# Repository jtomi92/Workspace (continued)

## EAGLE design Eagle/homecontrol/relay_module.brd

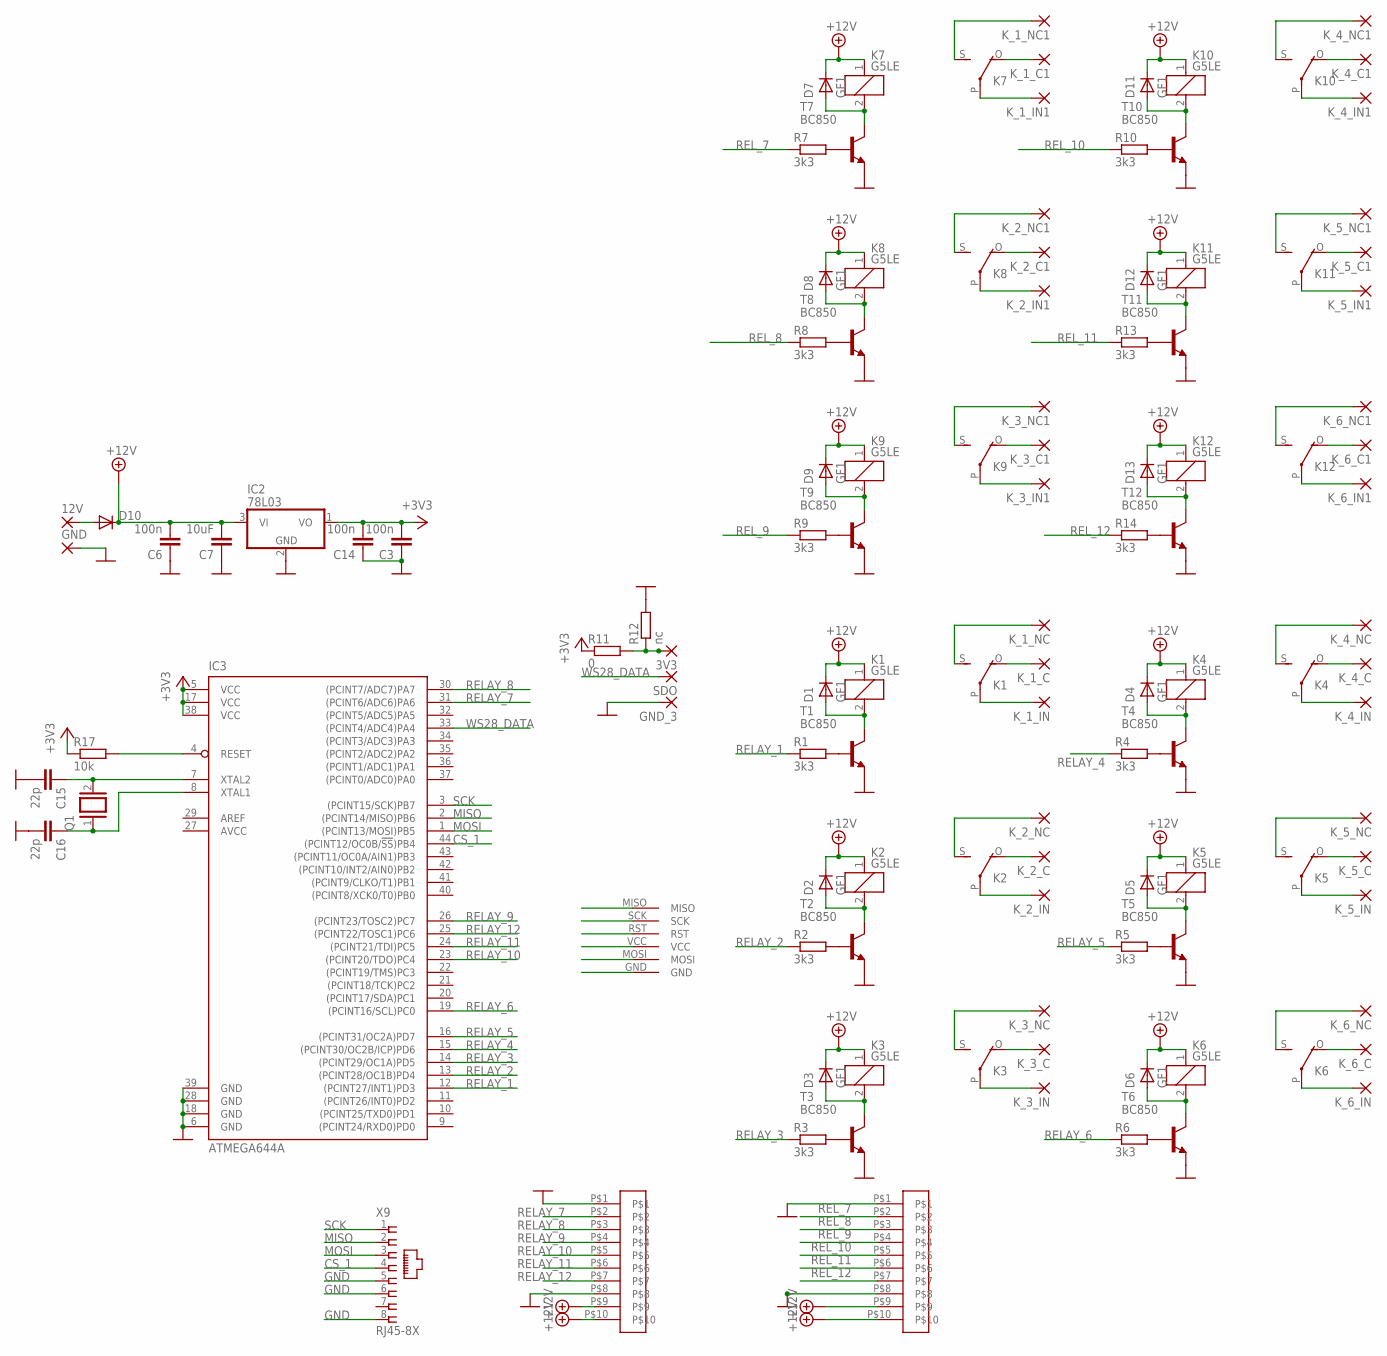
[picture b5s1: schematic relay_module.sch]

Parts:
3V3: 2,15/1,0
12V: 2,54/0,8
C3, C6, C14: 100n; C1206
C7: 10uF; C1206
C15, C16: 22p; C1206
D1, D2, D3, D4, D5, D6, D7, D8, D9, D11, D12, D13: GF1; SMA-DO214AC
D10: 1N4148DO35-10; DO35-10
GND: 2,54/0,8
GND_3: 2,15/1,0
IC2: 78L03; TO92
IC3: ATMEGA644A; TQFP44
K1, K2, K3, K4, K5, K6, K7, K8, K9, K10, K11, K12: G5LE
K_1_C, K_1_C1, K_1_IN, K_1_IN1, K_1_NC, K_1_NC1, K_2_C, K_2_C1, K_2_IN, K_2_IN1, K_2_NC, K_2_NC1, K_3_C, K_3_C1, K_3_IN, K_3_IN1, K_3_NC, K_3_NC1, K_4_C, K_4_C1, K_4_IN, K_4_IN1, K_4_NC, K_4_NC1, K_5_C, K_5_C1, K_5_IN, K_5_IN1, K_5_NC, K_5_NC1, K_6_C, K_6_C1, K_6_IN, K_6_IN1, K_6_NC, K_6_NC1: 2,54/0,8
Q1: XTAL/S; QS
R1, R2, R3, R4, R5, R6, R7, R8, R9, R10, R13, R14: 3k3; M3216
R11: 0; M3216
R12: nc; M3216
R17: 10k; M3216
SDO: 2,15/1,0
T1, T2, T3, T4, T5, T6, T7, T8, T9, T10, T11, T12: BC850; SOT23
U$1, U$3: 10P
U$2: AVR_ISP
X9: RJ45-8X; RJ45-NO-SHIELD

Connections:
+3V3: C3.2, C14.2, IC2.1 (VO), IC3.5 (VCC), IC3.17 (VCC), IC3.38 (VCC), R11.1, R17.1, U$2.VCC
+12V: C6.2, C7.2, D1.K (C), D2.K (C), D3.K (C), D4.K (C), D5.K (C), D6.K (C), D7.K (C), D8.K (C), D9.K (C), D10.C, D11.K (C), D12.K (C), D13.K (C), IC2.3 (VI), K1.1, K2.1, K3.1, K4.1, K5.1, K6.1, K7.1, K8.1, K9.1, K10.1, K11.1, K12.1, U$1.P$9, U$1.P$10, U$3.P$9, U$3.P$10
AVCC: IC3.27 (AVCC)
CS_1: IC3.44 ((PCINT12/OC0B/!SS!)PB4), X9.4
GND: C3.1, C6.1, C7.1, C14.1, C15.2, C16.2, GND.1, GND_3.1, IC2.2 (GND), IC3.6 (GND), IC3.18 (GND), IC3.28 (GND), IC3.39 (GND), R12.2, T1.2 (E), T2.2 (E), T3.2 (E), T4.2 (E), T5.2 (E), T6.2 (E), T7.2 (E), T8.2 (E), T9.2 (E), T10.2 (E), T11.2 (E), T12.2 (E), U$1.P$1, U$1.P$8, U$2.GND, U$3.P$1, U$3.P$8, X9.5, X9.6, X9.8
MISO: IC3.2 ((PCINT14/MISO)PB6), U$2.MISO, X9.2
MOSI: IC3.1 ((PCINT13/MOSI)PB5), U$2.MOSI, X9.3
unnamed: R1.2, T1.1 (B)
unnamed: D1.A, K1.2, T1.3 (C)
unnamed: K1.S, K_1_NC.1
unnamed: K1.P, K_1_IN.1
unnamed: K1.O, K_1_C.1
unnamed: R2.2, T2.1 (B)
unnamed: D2.A, K2.2, T2.3 (C)
unnamed: K2.P, K_2_IN.1
unnamed: K2.O, K_2_C.1
unnamed: K2.S, K_2_NC.1
unnamed: R3.2, T3.1 (B)
unnamed: D3.A, K3.2, T3.3 (C)
unnamed: K3.P, K_3_IN.1
unnamed: K3.O, K_3_C.1
unnamed: K3.S, K_3_NC.1
unnamed: R4.2, T4.1 (B)
unnamed: D4.A, K4.2, T4.3 (C)
unnamed: K4.P, K_4_IN.1
unnamed: K4.O, K_4_C.1
unnamed: K4.S, K_4_NC.1
unnamed: R5.2, T5.1 (B)
unnamed: D5.A, K5.2, T5.3 (C)
unnamed: K5.P, K_5_IN.1
unnamed: K5.O, K_5_C.1
unnamed: K5.S, K_5_NC.1
unnamed: R6.2, T6.1 (B)
unnamed: D6.A, K6.2, T6.3 (C)
unnamed: K6.P, K_6_IN.1
unnamed: K6.O, K_6_C.1
unnamed: K6.S, K_6_NC.1
unnamed: R7.2, T7.1 (B)
unnamed: D7.A, K7.2, T7.3 (C)
unnamed: K7.P, K_1_IN1.1
unnamed: K7.O, K_1_C1.1
unnamed: K7.S, K_1_NC1.1
unnamed: R8.2, T8.1 (B)
unnamed: D8.A, K8.2, T8.3 (C)
unnamed: K8.P, K_2_IN1.1
unnamed: K8.O, K_2_C1.1
unnamed: K8.S, K_2_NC1.1
unnamed: R9.2, T9.1 (B)
unnamed: D9.A, K9.2, T9.3 (C)
unnamed: K9.P, K_3_IN1.1
unnamed: K9.O, K_3_C1.1
unnamed: K9.S, K_3_NC1.1
unnamed: 3V3.1, R11.2, R12.1
unnamed: R10.2, T10.1 (B)
unnamed: D11.A, K10.2, T10.3 (C)
unnamed: K10.P, K_4_IN1.1
unnamed: 12V.1, D10.A
unnamed: K10.O, K_4_C1.1
unnamed: K10.S, K_4_NC1.1
unnamed: R13.2, T11.1 (B)
unnamed: D12.A, K11.2, T11.3 (C)
unnamed: K11.P, K_5_IN1.1
unnamed: K11.O, K_5_C1.1
unnamed: C15.1, IC3.7 (XTAL2), Q1.2
unnamed: K11.S, K_5_NC1.1
unnamed: R14.2, T12.1 (B)
unnamed: D13.A, K12.2, T12.3 (C)
unnamed: K12.P, K_6_IN1.1
unnamed: K12.O, K_6_C1.1
unnamed: K12.S, K_6_NC1.1
unnamed: C16.1, IC3.8 (XTAL1), Q1.1
RELAY_1: IC3.12 ((PCINT27/INT1)PD3), R1.1
RELAY_2: IC3.13 ((PCINT28/OC1B)PD4), R2.1
RELAY_3: IC3.14 ((PCINT29/OC1A)PD5), R3.1
RELAY_4: IC3.15 ((PCINT30/OC2B/ICP)PD6), R4.1
RELAY_5: IC3.16 ((PCINT31/OC2A)PD7), R5.1
RELAY_6: IC3.19 ((PCINT16/SCL)PC0), R6.1
RELAY_7: IC3.31 ((PCINT6/ADC6)PA6), U$1.P$2
RELAY_8: IC3.30 ((PCINT7/ADC7)PA7), U$1.P$3
RELAY_9: IC3.26 ((PCINT23/TOSC2)PC7), U$1.P$4
RELAY_10: IC3.23 ((PCINT20/TDO)PC4), U$1.P$5
RELAY_11: IC3.24 ((PCINT21/TDI)PC5), U$1.P$6
RELAY_12: IC3.25 ((PCINT22/TOSC1)PC6), U$1.P$7
REL_7: R7.1, U$3.P$2
REL_8: R8.1, U$3.P$3
REL_9: R9.1, U$3.P$4
REL_10: R10.1, U$3.P$5
REL_11: R13.1, U$3.P$6
REL_12: R14.1, U$3.P$7
RESET: IC3.4 (RESET), R17.2, U$2.RST
SCK: IC3.3 ((PCINT15/SCK)PB7), U$2.SCK, X9.1
WS28_DATA: IC3.33 ((PCINT4/ADC4)PA4), SDO.1

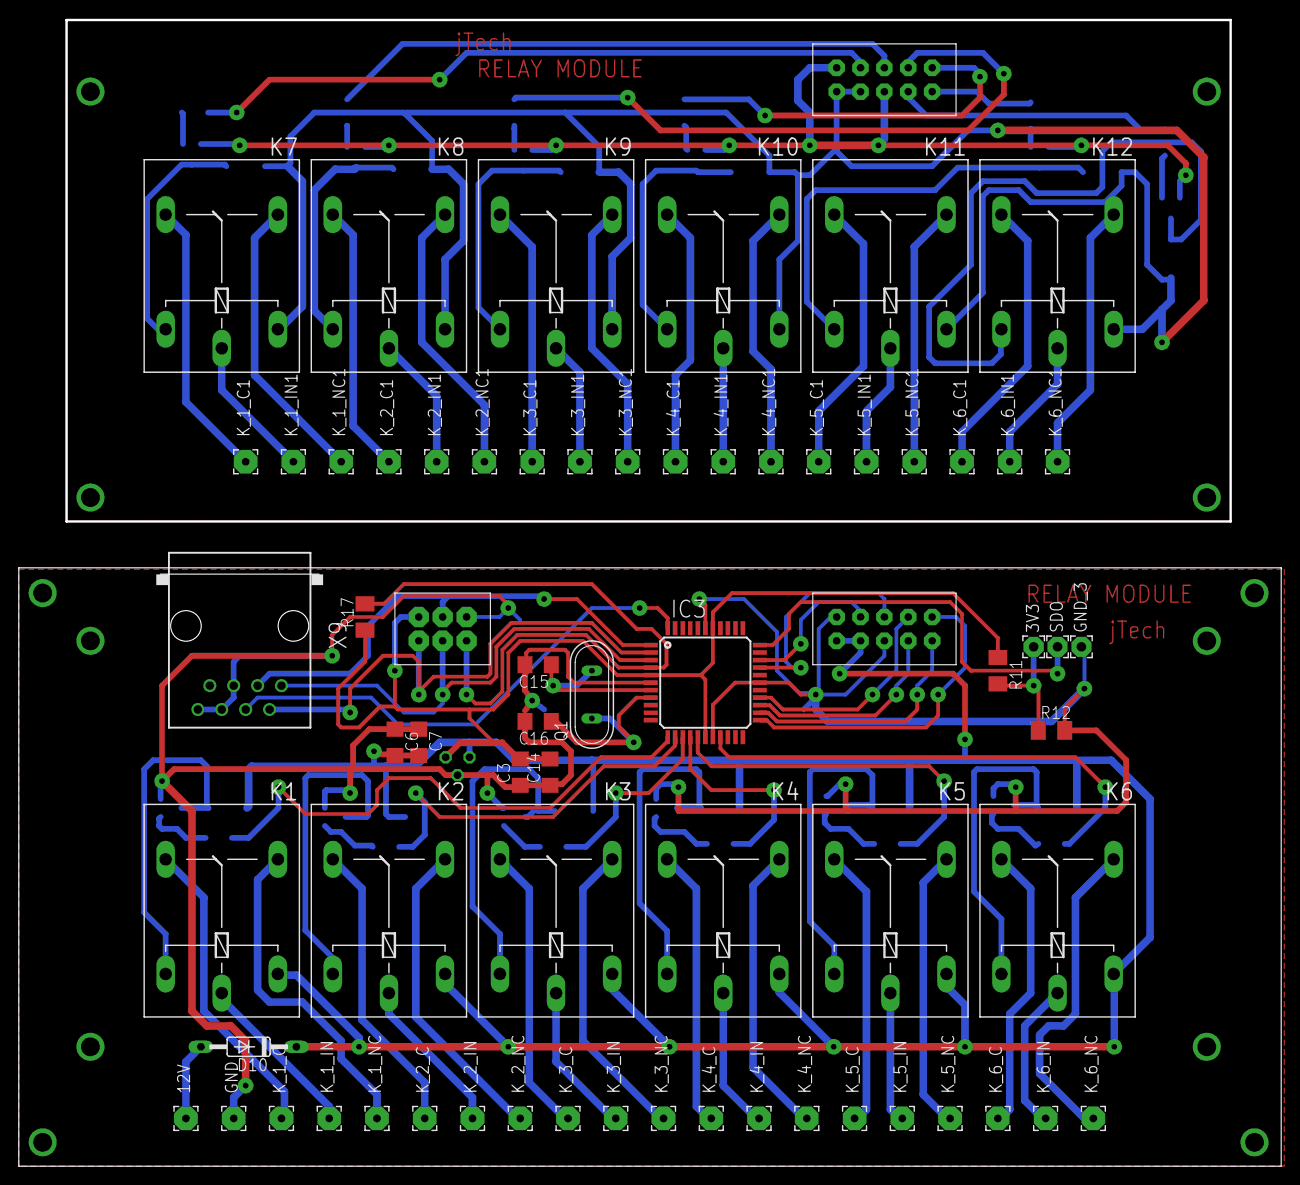
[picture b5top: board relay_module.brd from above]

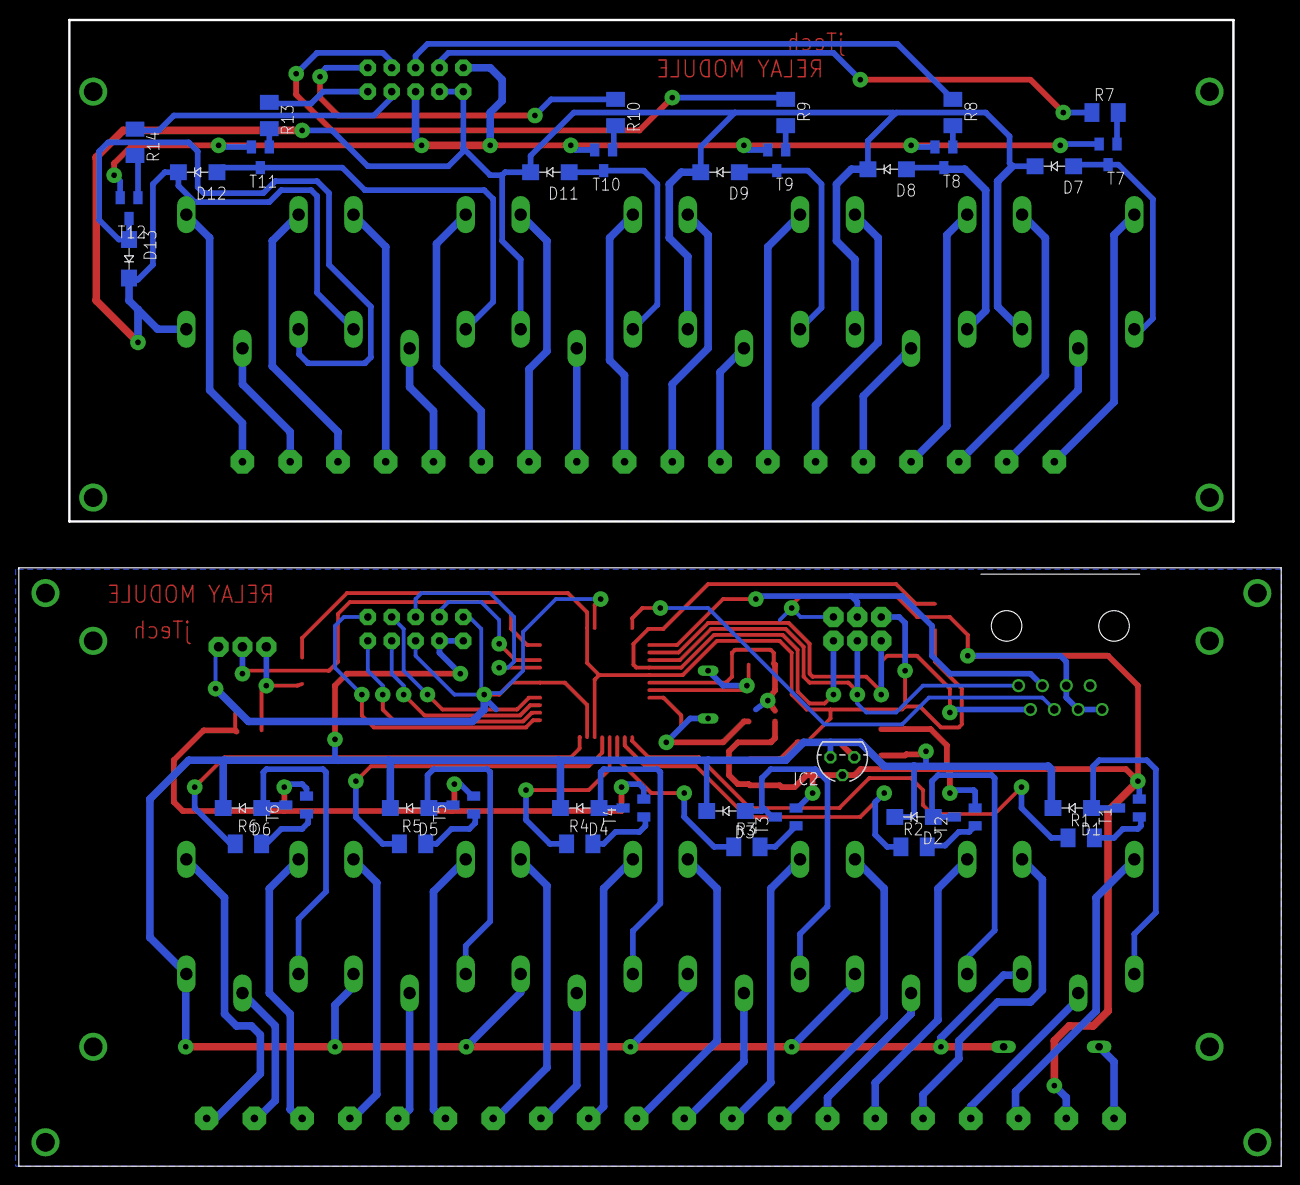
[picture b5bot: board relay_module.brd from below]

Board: 2 copper layers, 134.3 x 121.9 mm, 106 parts (37 on the bottom side), 91 nets.

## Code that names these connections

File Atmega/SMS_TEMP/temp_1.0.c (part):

#define RELAY_0 PORTB.B0
#define RELAY_1 PORTB.B1
#define RELAY_2 PORTB.B2
#define RELAY_3 PORTB.B3
#define RELAY_4 PORTB.B4
#define RELAY_5 PORTB.B5
#define RELAY_6 PORTE.B0
#define RELAY_7 PORTE.B1
#define RELAY_8 PORTE.B2

#define ESP_PWR PORTC.B3
#define SIM_PWR PORTC.B1

#define VCC_DETECT PORTA.B0
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
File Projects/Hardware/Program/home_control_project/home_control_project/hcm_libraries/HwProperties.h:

/*
 * HwProperties.h
 *
 * Created: 2016.09.30. 15:04:02
 *  Author: tjozsa
 */ 


#ifndef HWPROPERTIES_H_
#define HWPROPERTIES_H_
#endif
#ifndef MAX_MODULE_COUNT
#define MAX_MODULE_COUNT 4
#endif
#ifndef MAX_RELAY_COUNT
#define MAX_RELAY_COUNT 13 // use: max relay count + 1
#endif

extern const char PRODUCT_NAME[];

extern const char NETWORK_SSID[];
extern const char NETWORK_PASSW[];
extern const char NETWORK_HOST[];
extern const char NETWORK_PORT[];
extern const char NETWORK_APN[];
extern const int RECONNECT_TIMER;
extern const int CONNECTION;

extern const int EEPROM_SIZE; 
extern const int HAS_WIFI;
extern const int HAS_GSM;
extern const int HAS_WS28;

extern const int WIFI_DIRECTION;
extern const int GSM_DIRECTION;

extern const int EEPROM_SIZE;
extern const int EEPROM_CFG_START;
extern const int EEPROM_DATA_START;
extern const int EEPROM_SERIAL_START;

extern const int SIM_PWR;
extern const int ESP_PWR;
extern const int WS28_DATA;
extern const int VCC_DETECT;
extern const int CS_1;
extern const int CS_2;
extern const int CS_3;
extern const int CS_4;
extern const int DETECT_0;
extern const int DETECT_1;
extern const int DETECT_2;
extern const int DETECT_3;
extern const int SCK;
extern const int MOSI;
extern const int MISO;
extern const int SS;

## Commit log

2017-01-06 :circus_tent: Added .gitattributes & .gitignore files
2017-01-06 Commit
    ALL THE CODE
2017-01-08 asd
    asd
2017-01-12 commit
    commit
2017-01-15 fix
    fix
2017-03-06 Commit
    updates
